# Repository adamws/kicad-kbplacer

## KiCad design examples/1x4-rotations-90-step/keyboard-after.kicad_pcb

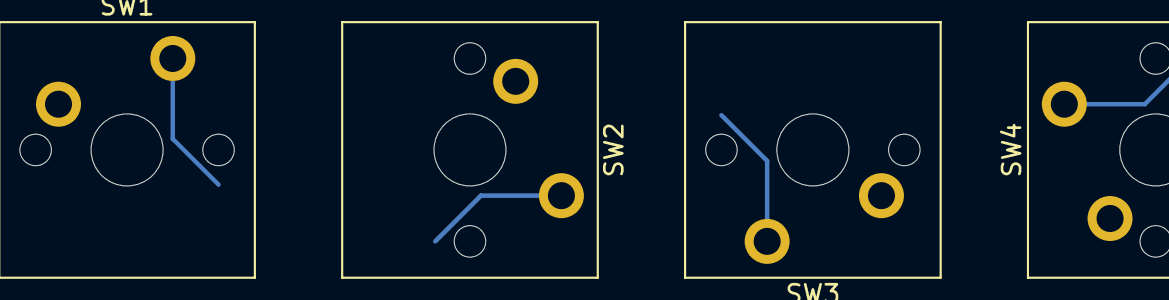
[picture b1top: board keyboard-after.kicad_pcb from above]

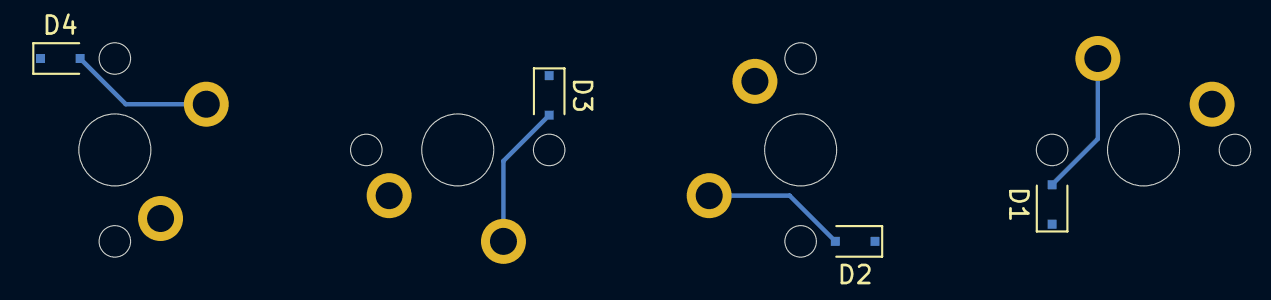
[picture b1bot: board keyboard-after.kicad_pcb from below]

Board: 2 copper layers, 8 parts (4 on the bottom side), 5 nets.

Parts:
D1, D2, D3, D4: D; D_SOD-323F
SW1, SW2, SW3, SW4: SW_Push; SW_Cherry_MX_PCB_1.00u

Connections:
unnamed: D1.2, SW1.2
unnamed: D2.2, SW2.2
unnamed: D3.2, SW3.2
unnamed: D4.2, SW4.2
ROW0: D1.1, D2.1, D3.1, D4.1
